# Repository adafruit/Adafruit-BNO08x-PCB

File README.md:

## Adafruit BNO085  9-DOF Orientation IMU Fusion Breakout PCB

<a href="http://www.adafruit.com/products/4754"><br/>
Click here to purchase one from the Adafruit shop</a>

PCB files for the Adafruit BNO085  9-DOF Orientation IMU Fusion Breakout. 

Format is EagleCAD schematic and board layout
* https://www.adafruit.com/product/4754

### Description

### License

Adafruit invests time and resources providing this open source design, please support Adafruit and open-source hardware by purchasing products from [Adafruit](https://www.adafruit.com)!

Designed by Limor Fried/Ladyada for Adafruit Industries.

Creative Commons Attribution/Share-Alike, all text above must be included in any redistribution. 
See license.txt for additional details.

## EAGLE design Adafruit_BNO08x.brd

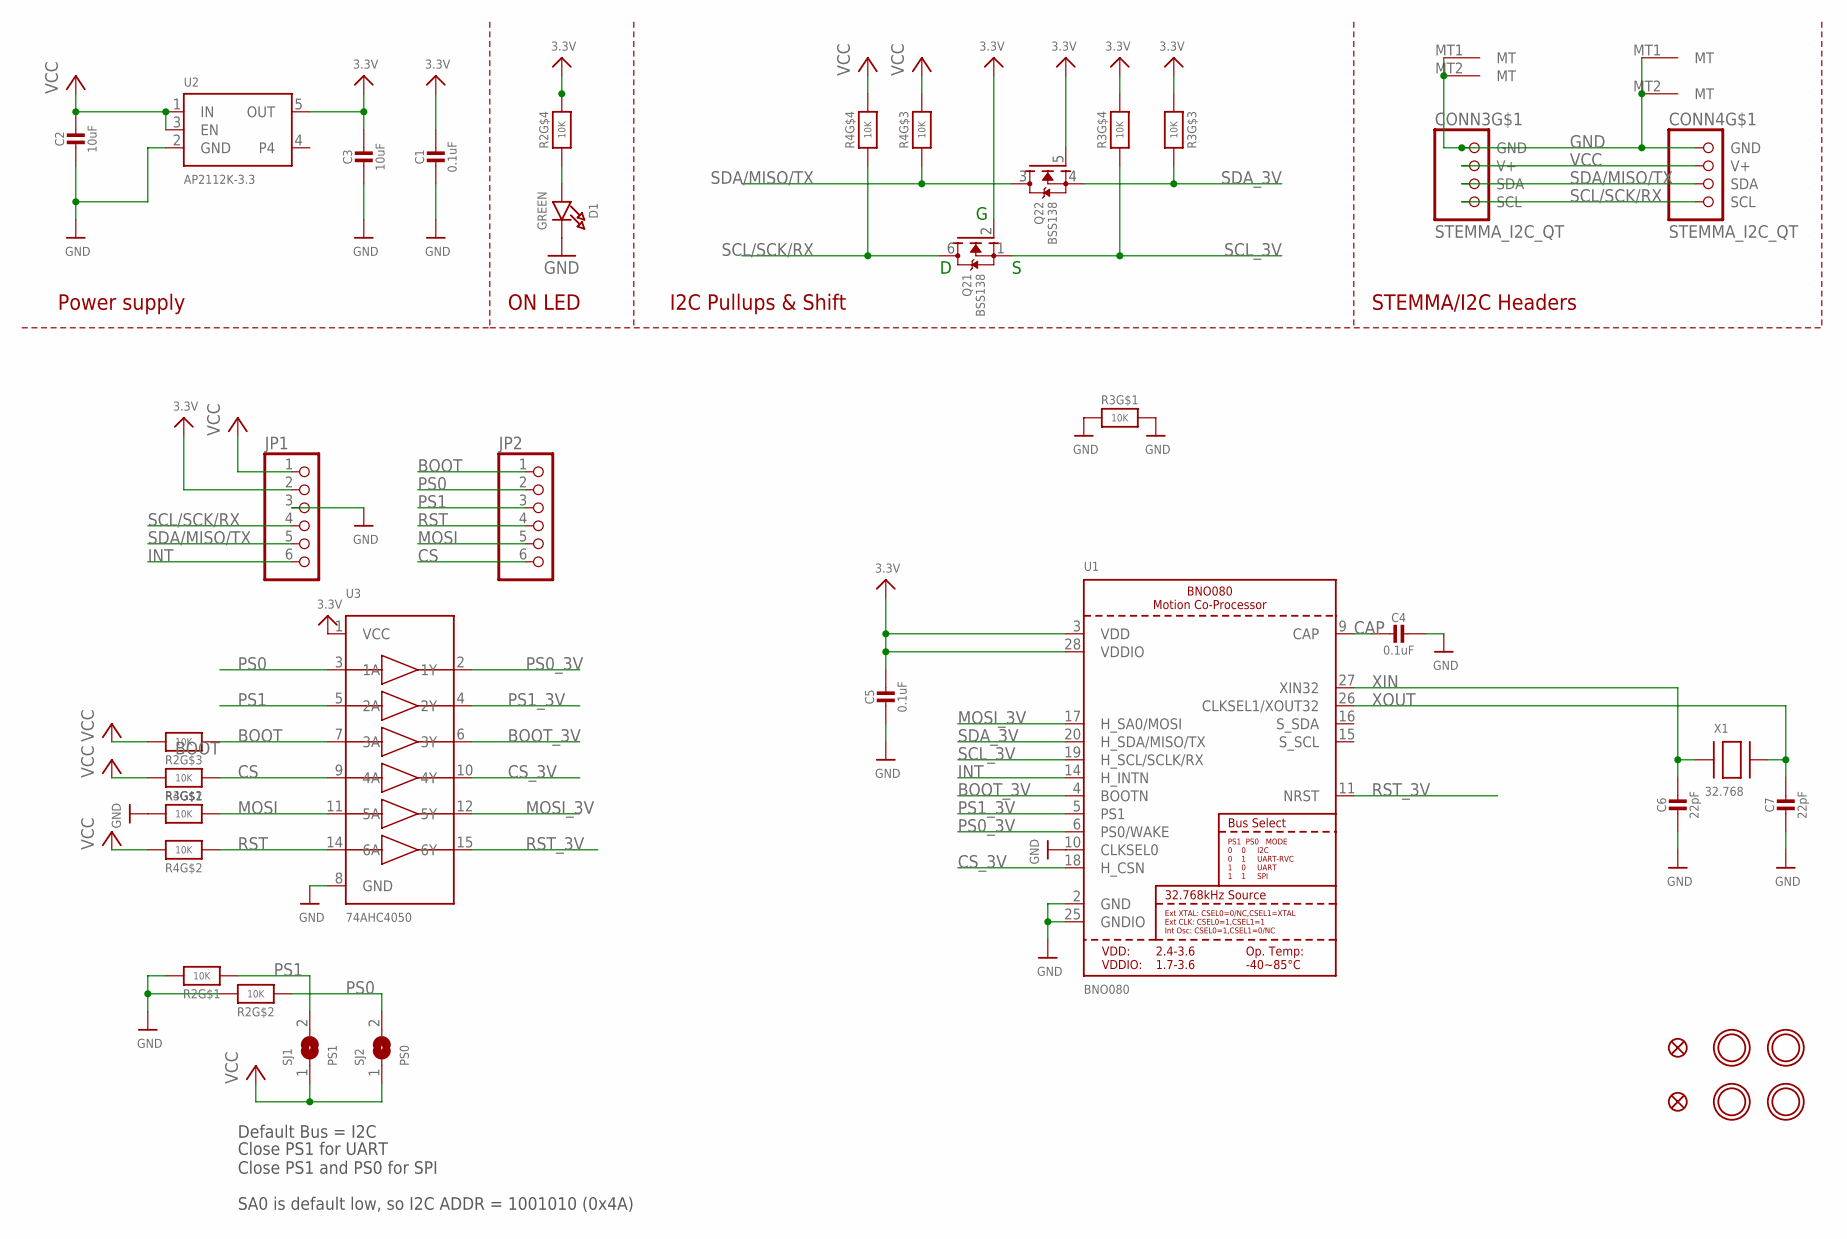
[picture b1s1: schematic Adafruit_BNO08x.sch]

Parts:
C1, C4, C5: 0.1uF; 0603-NO
C2, C3: 10uF; 0805-NO
C6, C7: 22pF; 0603-NO
CONN3, CONN4: STEMMA_I2C_QT; JST_SH4
D1: GREEN; CHIPLED_0603_NOOUTLINE
FID3, FID4: FIDUCIAL_1MM
JP1, JP2: HEADER-1X670MIL; 1X06_ROUND_70
Q2: BSS138; SOT363
R2, R3, R4: 10K; RESPACK_4X0603
SJ1: PS1; SOLDERJUMPER_ARROW_NOPASTE
SJ2: PS0; SOLDERJUMPER_ARROW_NOPASTE
U1: BNO080
U2: AP2112K-3.3; SOT23-5
U3: 74AHC4050; TSSOP16
U$1, U$17, U$19, U$21: MOUNTINGHOLE2.5; MOUNTINGHOLE_2.5_PLATED
X1: 32.768; XTAL3215

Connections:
3.3V: C1.1, C3.1, C5.1, JP1.2, Q2.2 (G), Q2.5 (G), R2.5 (2), R3.3 (1), R3.5 (2), U1.3 (VDD), U1.28 (VDDIO), U2.5 (OUT), U3.1 (VCC)
BOOT: JP2.1, R2.3 (1), U3.7 (3A)
BOOT_3V: U1.4 (BOOTN), U3.6 (3Y)
CAP: C4.2, U1.9 (CAP)
CS: JP2.6, R4.1, U3.9 (4A)
CS_3V: U1.18 (H_CSN), U3.10 (4Y)
GND: C1.2, C2.2, C3.2, C4.1, C5.2, C6.2, C7.2, CONN3.1 (GND), CONN3.MT1 (MT), CONN3.MT2 (MT), CONN4.1 (GND), CONN4.MT1 (MT), CONN4.MT2 (MT), D1.C, JP1.3, R2.7 (2), R2.8 (2), R3.1, R3.2 (1), R3.8 (2), U1.2 (GND), U1.10 (CLKSEL0), U1.25 (GNDIO), U2.2 (GND), U3.8 (GND)
INT: JP1.6, U1.14 (H_INTN)
MOSI: JP2.5, R3.7 (2), U3.11 (5A)
MOSI_3V: U1.17 (H_SA0/MOSI), U3.12 (5Y)
unnamed: D1.A, R2.4 (1)
PS0: JP2.2, R2.2 (1), SJ2.2, U3.3 (1A)
PS0_3V: U1.6 (PS0/WAKE), U3.2 (1Y)
PS1: JP2.3, R2.1, SJ1.2, U3.5 (2A)
PS1_3V: U1.5 (PS1), U3.4 (2Y)
RST: JP2.4, R4.2 (1), U3.14 (6A)
RST_3V: U1.11 (NRST), U3.15 (6Y)
SCL/SCK/RX: CONN3.4 (SCL), CONN4.4 (SCL), JP1.4, Q2.6 (D), R4.4 (1)
SCL_3V: Q2.1 (S), R3.4 (1), U1.19 (H_SCL/SCLK/RX)
SDA/MISO/TX: CONN3.3 (SDA), CONN4.3 (SDA), JP1.5, Q2.3 (D), R4.3 (1)
SDA_3V: Q2.4 (S), R3.6 (2), U1.20 (H_SDA/MISO/TX)
VCC: C2.1, CONN3.2 (V+), CONN4.2 (V+), JP1.1, R2.6 (2), R4.5 (2), R4.6 (2), R4.7 (2), R4.8 (2), SJ1.1, SJ2.1, U2.1 (IN), U2.3 (EN)
XIN: C6.1, U1.27 (XIN32), X1.P$1
XOUT: C7.1, U1.26 (CLKSEL1/XOUT32), X1.P$2

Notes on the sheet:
I2C Pullups & Shift
STEMMA/I2C Headers
ON LED
Power supply
Default Bus = I2C
Close PS1 for UART Close PS1 and PS0 for SPI
SA0 is default low, so I2C ADDR = 1001010 (0x4A)

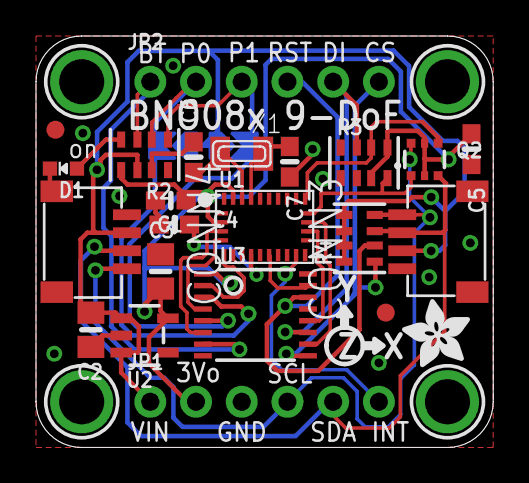
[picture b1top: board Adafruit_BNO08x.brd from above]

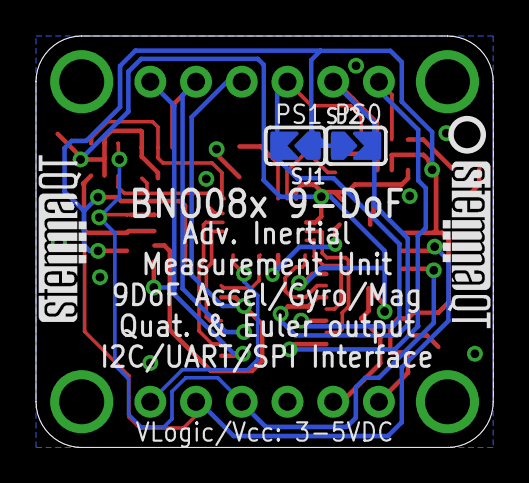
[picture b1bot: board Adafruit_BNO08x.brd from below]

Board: 2 copper layers, 25.4 x 22.9 mm, 32 parts (5 on the bottom side), 24 nets.

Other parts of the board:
U$22: ADAFRUIT_3.5MM
U$25: PCBFEAT-REV-040
U$30, U$31: STEMMAQT

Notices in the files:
parts and their libraries:
microbuilder: This work is placed in the public domain, and may be freely used for commercial and non-commercial work with the following conditions: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
